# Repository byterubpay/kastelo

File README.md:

# Kastelo
This is the project to create an official ByteRub Hardware Wallet

1. [Safe, Vault](https://en.wikipedia.org/wiki/Esperanto), a place to store valuables
2. An open hardware ByteRub wallet

## Are you a tester looking for FW?
Please go to firmware/monezor and read the README there

## Disclaimers
- No hardware available
- Currently in the design and pre-fabrication stage

## Documentation
- Project documentation is being written
- [ByteRubpedia](https://getbyterub.org/knowledge-base/byterubpedia/) is recommended for a general introduction to the ByteRub-verse

## Developers
- Contributing advice is found in CONTRIBUTING.md (please review before submitting a pull request)

### Project Management
Follow the engineering pace of our project at:

[https://taiga.getbyterub.org/project/michael-rfc-hwallet-1-implementation/](https://taiga.getbyterub.org/project/michael-rfc-hwallet-1-implementation/)

## Support
- IRC: [Freenode](irc://chat.freenode.net/#byterub-hardware/)
- [ByteRub StackExchange](https://byterub.stackexchange.com/)
- [Mattermost](https://mattermost.getbyterub.org/byterub/channels/byterubhardware/)

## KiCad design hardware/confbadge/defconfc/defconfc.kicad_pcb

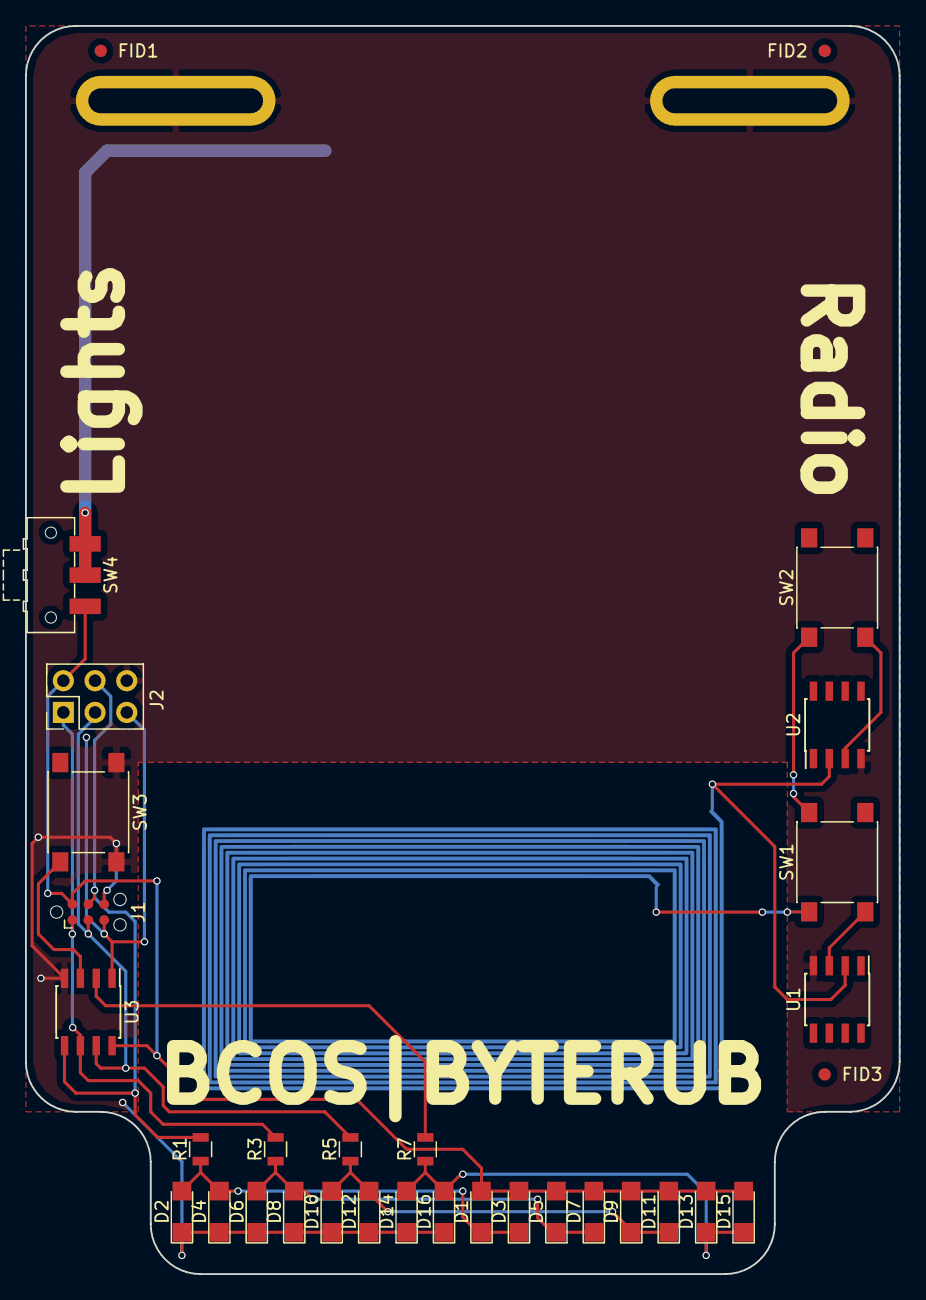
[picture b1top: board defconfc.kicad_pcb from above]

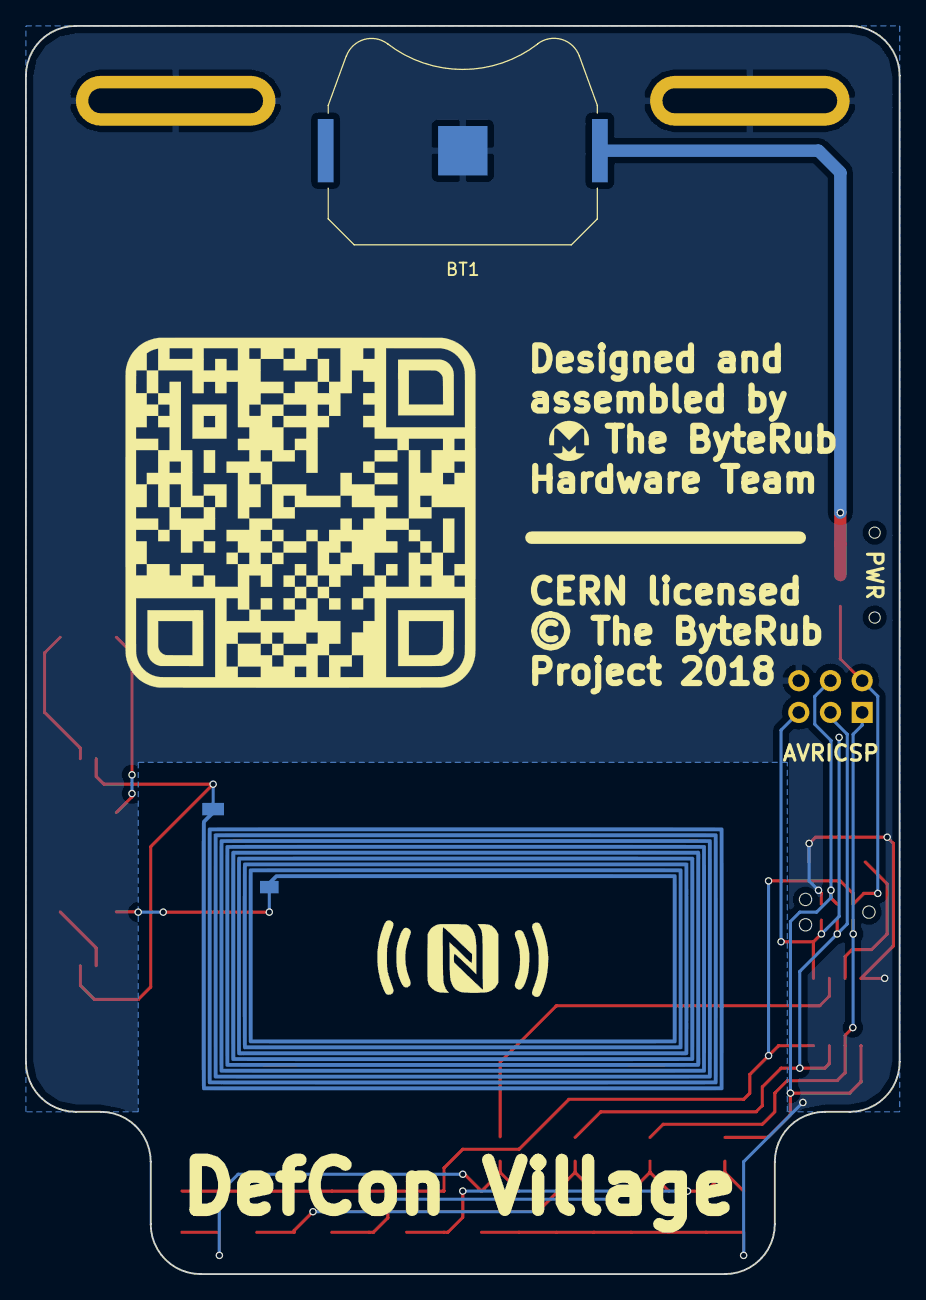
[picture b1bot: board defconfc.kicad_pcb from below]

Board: 2 copper layers, 70.0 x 100.0 mm, 39 parts (5 on the bottom side), 17 nets.

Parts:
AE1: Antenna_PCB; NFCAntennaloop
BT1: Battery_Cell; Keystone_3034_1x2032-Coincell
D1, D2, D3, D4, D5, D6, D7, D8, D9, D10, D11, D12, D13, D14, D15, D16: LED; LED_1206
FID1, FID2, FID3: Fiducial_Passermarke; Fiducial_1mm_Dia_2mm_Outer
G1: NFCRadiate; NFCGraphicsrear
G2: Kastelospecs; Kastelospecsqrcode
J1: Conn_02x03_Odd_Even; Tag-Connect_TC2030-IDC-NL
J2: Conn_02x03_Odd_Even; Pin_Header_Straight_2x03_Pitch2.54mm
L2: Graphbrand; ByteRublogokreis
LH1, LH2: Mounting-Lanyard; LanyardHole_16mm_Pad
R1, R3, R5, R7: 220; R_0805
SW1, SW2, SW3: SW_SPST; SW_SPST_PTS645
SW4: SW_SPDT; SW_SPDT_CK-JS102011SAQN
U1, U2: M24SR16-YMN6T/2; SOIC-8_3.9x4.9mm_Pitch1.27mm
U3: ATTINY13A-SSU; SOIC-8_3.9x4.9mm_Pitch1.27mm

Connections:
GND: BT1.2, D2.1, D4.1, D6.1, D8.1, D10.1, D12.1, D14.1, D16.1, J1.6, J2.6, LH1.1, LH2.1, SW3.2, U1.4, U2.4, U3.4
MISO: J1.1, J2.1, R3.2, U3.6
MOSI: J1.4, J2.4, R1.2, U3.5
unnamed: AE1.1, U1.2, U2.2
unnamed: AE1.2, SW1.1, SW2.1
unnamed: BT1.1, SW4.1, SW4.2
unnamed: D1.1, D2.2, D3.1, D4.2, R1.1
unnamed: D5.1, D6.2, D7.1, D8.2, R3.1
unnamed: D9.1, D10.2, D11.1, D12.2, R5.1
unnamed: D13.1, D14.2, D15.1, D16.2, R7.1
unnamed: SW1.2, U1.3
unnamed: SW2.2, U2.3
unnamed: SW3.1, U3.3
PB3: R7.2, U3.2
RST: J1.5, J2.5, U3.1
SCK: J1.3, J2.3, R5.2, U3.7
VCC: D1.2, D3.2, D5.2, D7.2, D9.2, D11.2, D13.2, D15.2, J1.2, J2.2, SW4.3, U3.8

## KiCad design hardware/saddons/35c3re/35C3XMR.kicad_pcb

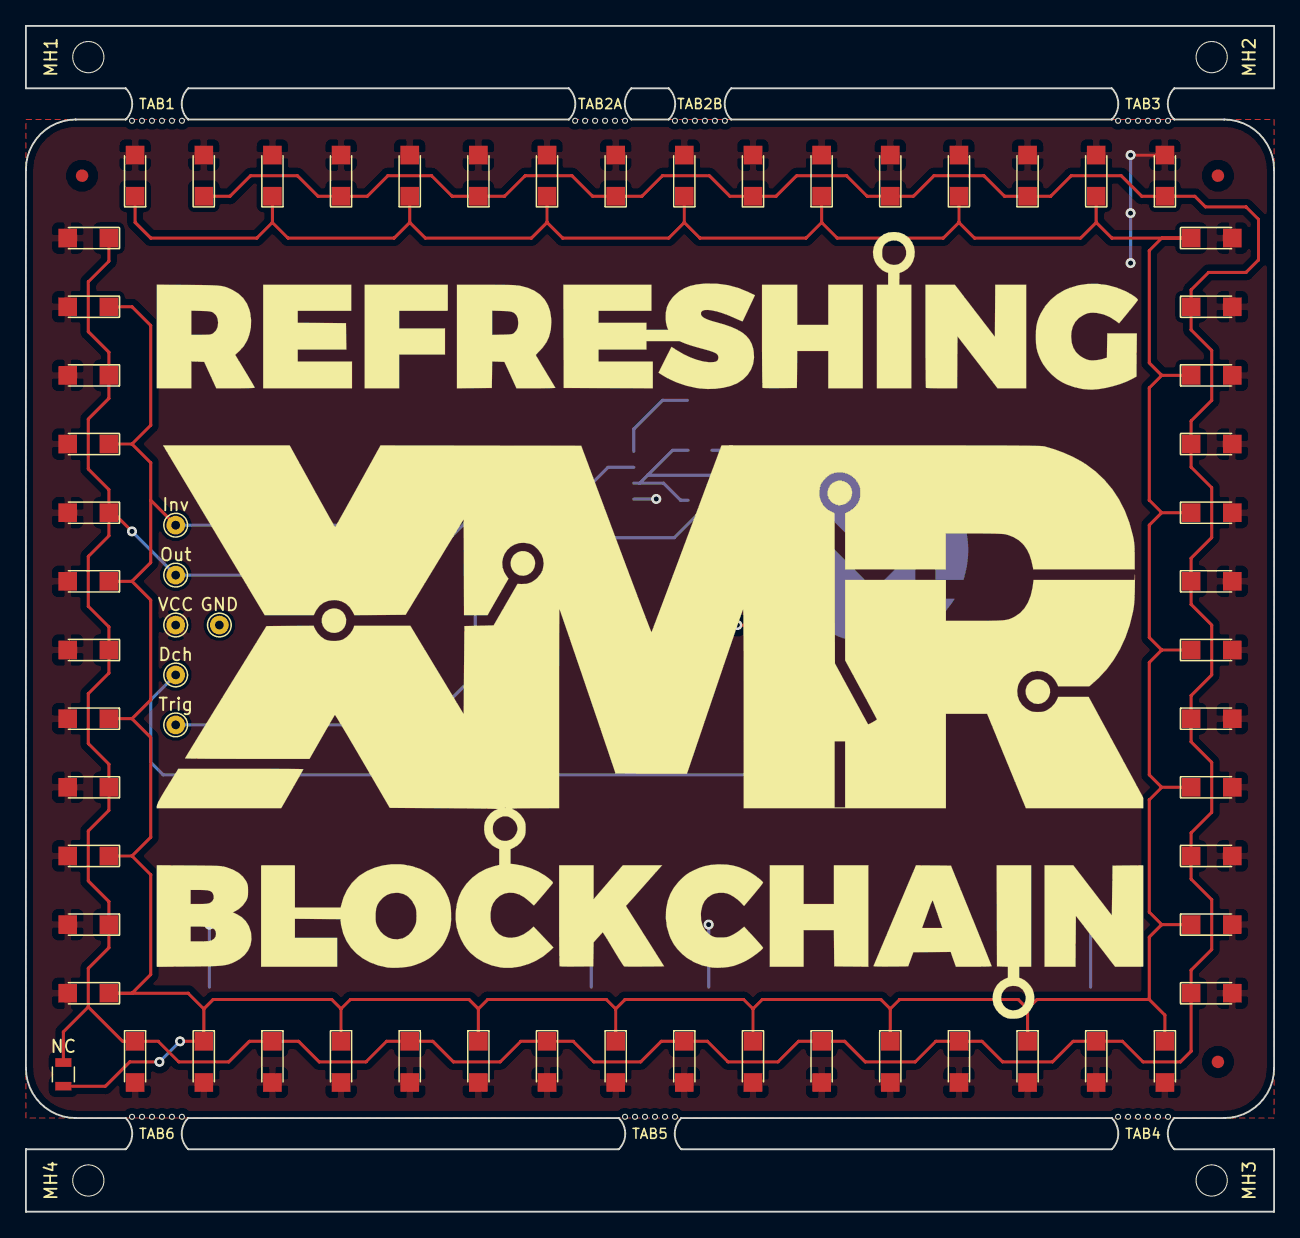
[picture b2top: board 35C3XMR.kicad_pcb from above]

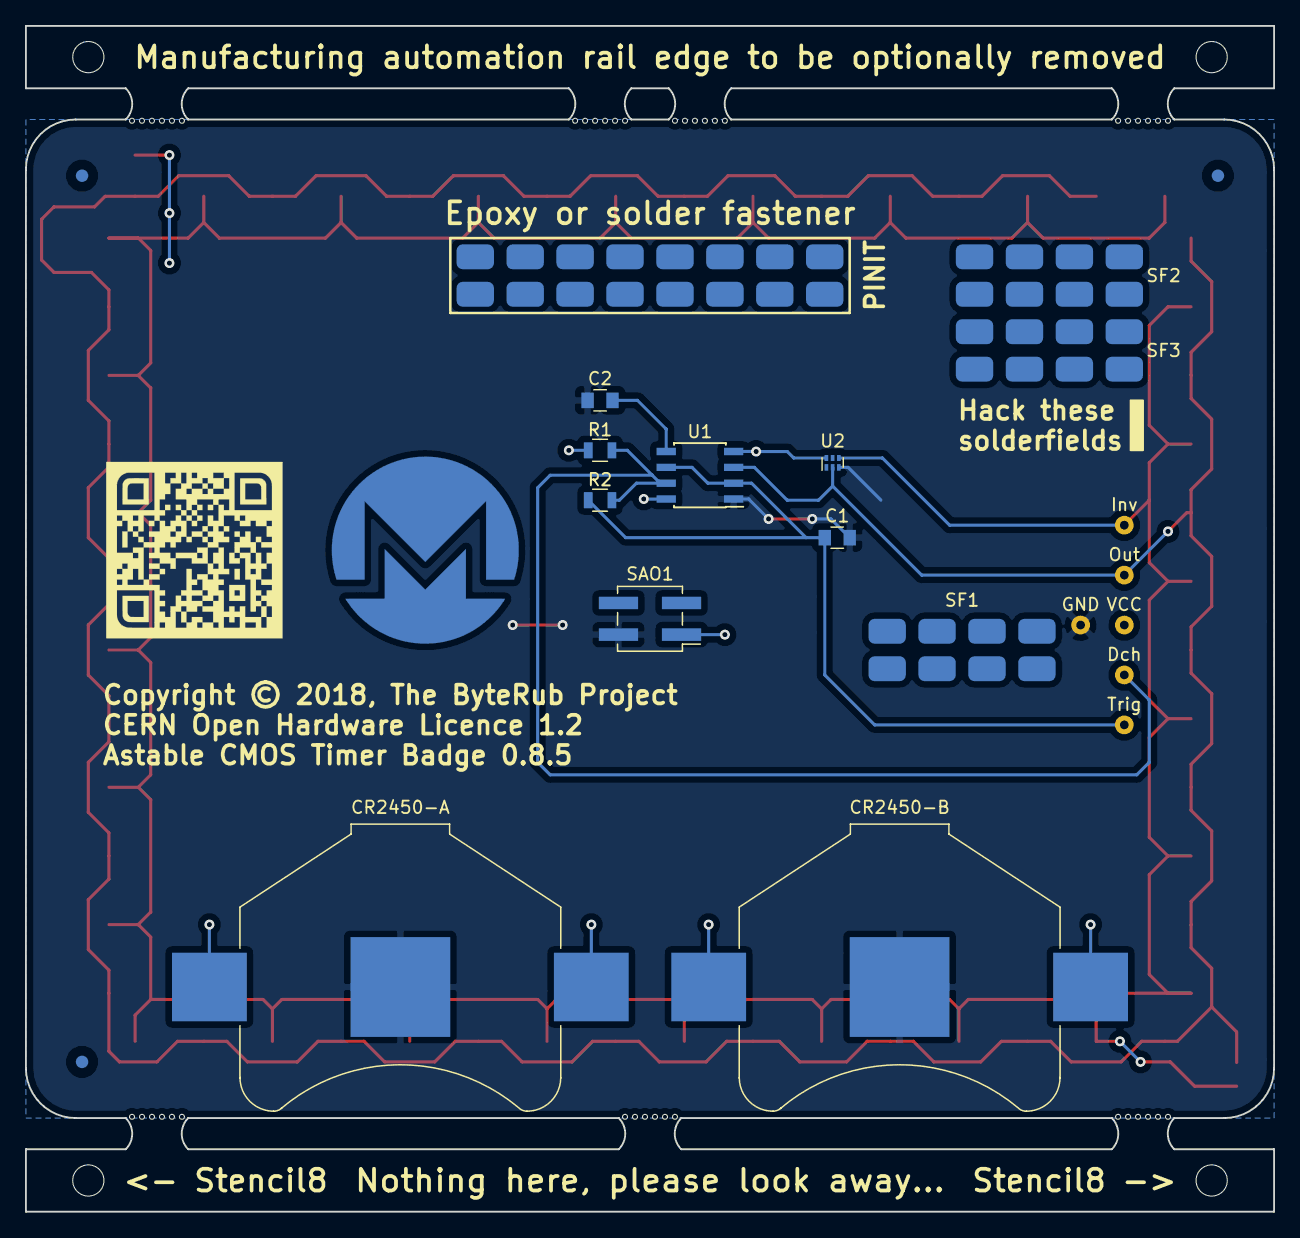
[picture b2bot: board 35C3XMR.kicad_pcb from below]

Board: 2 copper layers, 100.0 x 95.0 mm, 97 parts (19 on the bottom side), 7 nets.

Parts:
C1: 4,7uF; C_0805
C2: ,01uF; C_0805
CR2450-A, CR2450-B: Battery_Cell; BatteryHolder_Keystone_3008_1x2450
D1, D2, D3, D4, D5, D6, D7, D8, D9, D10, D11, D12, D13, D14, D15, D16, D17, D18, D19, D20, D21, D22, D23, D24, D25, D26, D27, D28, D29, D30, D31, D32, D33, D34, D35, D36, D37, D38, D39, D40, D41, D42, D43, D44, D45, D46, D47, D48, D49, D50, D51, D52, D53, D54, D55, D56: LED; LED_1206
Dch: TEST; TestPoint_THTPad_D1.5mm_Drill0.7mm
FID1, FID3, FID5: FiducialPassermarke-Top; Fiducial_1mm_Dia_2.54mm
FID2, FID4, FID6: FiducialPassermarke-Bot; Fiducial_1mm_Dia_2.54mm
G1: QRCOD; Kastelospecsqr
GND: TEST; TestPoint_THTPad_D1.5mm_Drill0.7mm
Inv: TEST; TestPoint_THTPad_D1.5mm_Drill0.7mm
LOGO1: 35C3Logo-funny; 35C3Funny
LOGO2: ByteRubball; ByteRubball_15mm
MH1, MH2, MH3, MH4: MountingHole_2.5mm
NC: Jumper; R_0805
Out: TEST; TestPoint_THTPad_D1.5mm_Drill0.7mm
R1: 10K; R_0805
R2: 100K; R_0805
SAO1: Shitty_conn; PinHeader_2x02_P2.54mm_Vertical_SMD
SF1, SF2, SF3, SF4, SF5: Soldfeld; Solderarea
TAB1, TAB2A, TAB2B, TAB3, TAB4, TAB5, TAB6: Panel_Mousetab_25mm_Single
Trig: TEST; TestPoint_THTPad_D1.5mm_Drill0.7mm
U1: TLC555; SOIC-8_3.9x4.9mm_P1.27mm
U2: NC7SZ04L6X; Fairchild_MicroPak-6_1.0x1.45mm_P0.5mm
VCC: TEST; TestPoint_THTPad_D1.5mm_Drill0.7mm

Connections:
+3V3: CR2450-A.1, CR2450-B.1, D1.2, D2.2, D3.2, D4.2, D5.2, D6.2, D7.2, D8.2, D9.2, D10.2, D11.2, D12.2, D13.2, D14.2, D15.2, D16.2, D17.2, D18.2, D19.2, D20.2, D21.2, D22.2, D23.2, D24.2, D25.2, D26.2, D27.2, D28.2, D29.2, D30.2, D31.2, D32.2, D33.2, D34.2, D35.2, D36.2, D37.2, D38.2, D39.2, D40.2, D41.2, D42.2, D43.2, D44.2, D45.2, D46.2, D47.2, D48.2, D49.2, D50.2, D51.2, D52.2, D53.2, D54.2, D55.2, D56.2, R1.2, SAO1.1, U1.4, U1.8, U2.6, VCC.1
GND: C1.2, C2.2, CR2450-A.2, CR2450-B.2, GND.1, SAO1.2, U1.1, U2.3
unnamed: C1.1, R2.2, Trig.1, U1.2, U1.6
unnamed: C2.1, U1.5
unnamed: D1.1, D3.1, D5.1, D7.1, D9.1, D11.1, D13.1, D15.1, D17.1, D19.1, D21.1, D23.1, D25.1, D27.1, D29.1, D31.1, D33.1, D35.1, D37.1, D39.1, D41.1, D43.1, D45.1, D47.1, D49.1, D51.1, D53.1, D55.1, Inv.1, NC.2, U2.4
unnamed: D2.1, D4.1, D6.1, D8.1, D10.1, D12.1, D14.1, D16.1, D18.1, D20.1, D22.1, D24.1, D26.1, D28.1, D30.1, D32.1, D34.1, D36.1, D38.1, D40.1, D42.1, D44.1, D46.1, D48.1, D50.1, D52.1, D54.1, D56.1, NC.1, Out.1, U1.3, U2.2
unnamed: Dch.1, R1.1, R2.1, U1.7

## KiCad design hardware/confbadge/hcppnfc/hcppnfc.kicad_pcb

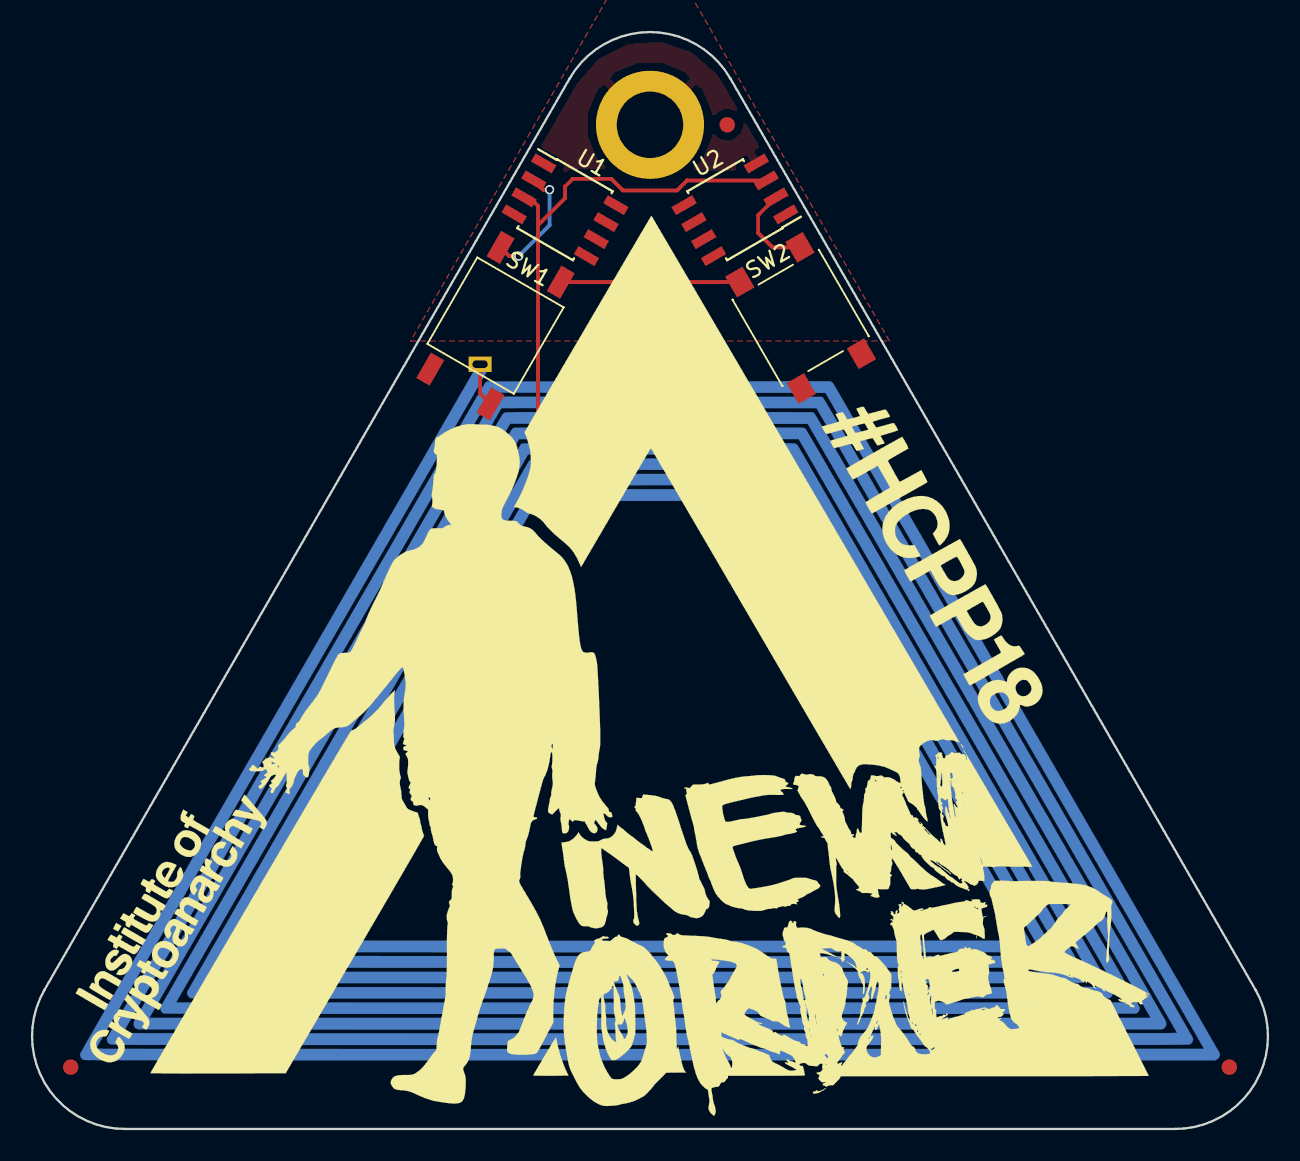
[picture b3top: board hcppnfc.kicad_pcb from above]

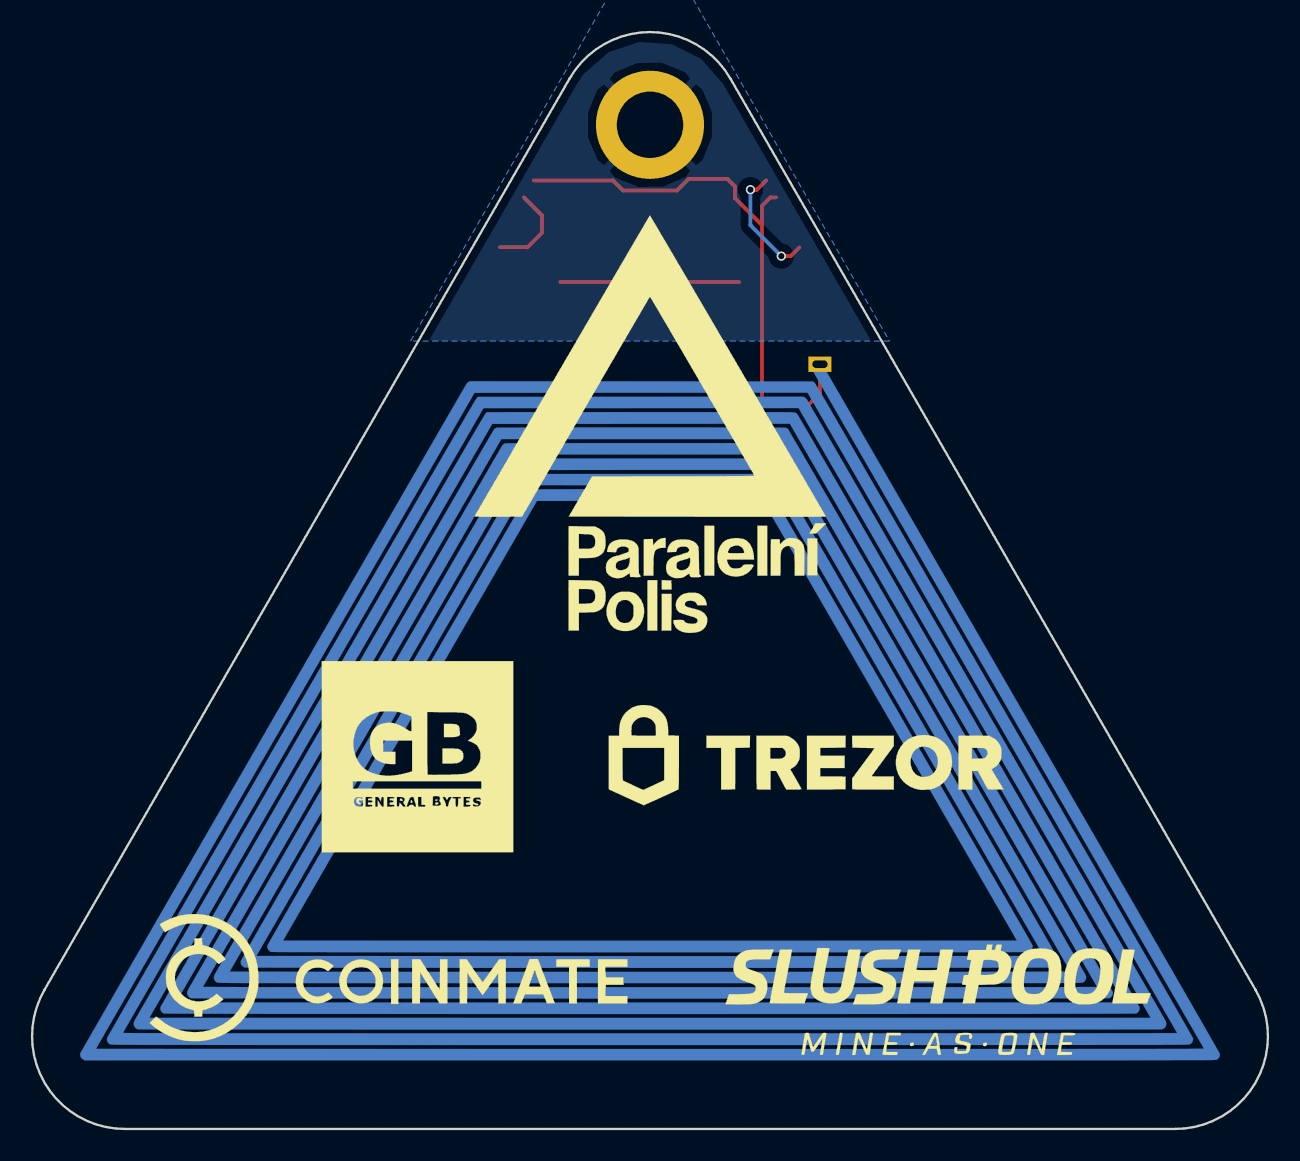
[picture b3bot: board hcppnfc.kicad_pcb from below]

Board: 2 copper layers, 80.0 x 71.0 mm, 13 parts (2 on the bottom side), 6 nets.

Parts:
AE1: Antenna_Loop; NFCAntennatall
FID1, FID2, FID3: Dummy_FIDUCIAL_Passermarke_Type1_RevE_Date16Nov20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; Fiducial_1mm_Dia_2mm_Outer
GFX*: ART_TRIANGLE; HCPPNewordtri
GFX*#2: ART_CONFYEAR; HCPPNewordconf
GFX*#3: ART_INSTCRYP; HCPPNewordinst
LOGO*: LOGO; HCPPSponsors
MH1: DUMMY_MOUNTING-HOLE_RevE_Date22jun2010; MountingHole_4.3mm_M4_ISO14580_Pad
SW1: SW_SPST; SW_SPST_K21102SP
SW2: SW_SPST; SW_SPST_PTS645
U1, U2: M24SR02-YMN; SOIC-8_3.9x4.9mm_Pitch1.27mm

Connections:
/ANTCON: AE1.2, U1.3, U2.3
GND: MH1.1, U1.4, U2.4
unnamed: AE1.1, SW1.1, SW2.1
unnamed: SW1.2, U1.2
unnamed: SW2.2, U2.2
VCC: U1.8, U2.8

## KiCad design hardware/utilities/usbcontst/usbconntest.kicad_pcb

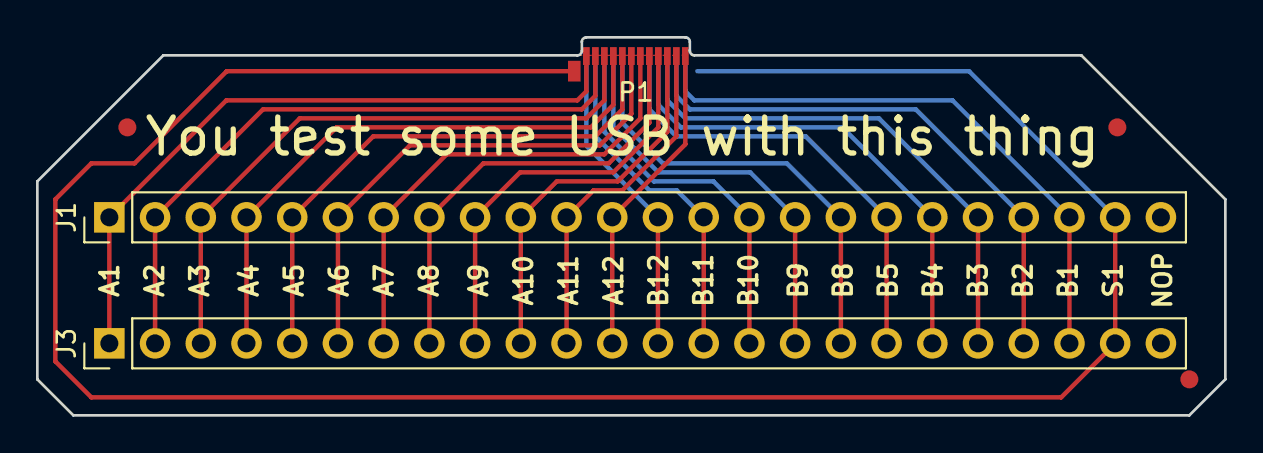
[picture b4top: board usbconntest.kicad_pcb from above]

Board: 2 copper layers, 66.0 x 21.0 mm, 6 parts (0 on the bottom side), 23 nets.

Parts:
FID1, FID2, FID3: Dummy_FIDUCIAL_Passermarke_Type1_RevE_Date16Nov20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; Fiducial_1mm_Dia_2mm_Outer
J1, J3: CONN_01X24; Pin_Header_Straight_1x24_Pitch2.54mm
P1: USB_C_Plug; USB_C_Plug_Molex_105444

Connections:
/A1: J1.1, J3.1, P1.A1
/A2: J1.2, J3.2, P1.A2
/A3: J1.3, J3.3, P1.A3
/A4: J1.4, J3.4, P1.A4
/A5: J1.5, J3.5, P1.A5
/A6: J1.6, J3.6, P1.A6
/A7: J1.7, J3.7, P1.A7
/A8: J1.8, J3.8, P1.A8
/A9: J1.9, J3.9, P1.A9
/A10: J1.10, J3.10, P1.A10
/A11: J1.11, J3.11, P1.A11
/A12: J1.12, J3.12, P1.A12
/B1: J1.22, J3.22, P1.B1
/B2: J1.21, J3.21, P1.B2
/B3: J1.20, J3.20, P1.B3
/B4: J1.19, J3.19, P1.B4
/B5: J1.18, J3.18, P1.B5
/B8: J1.17, J3.17, P1.B8
/B9: J1.16, J3.16, P1.B9
/B10: J1.15, J3.15, P1.B10
/B11: J1.14, J3.14, P1.B11
/B12: J1.13, J3.13, P1.B12
/S1: J1.23, J3.23, P1.S1

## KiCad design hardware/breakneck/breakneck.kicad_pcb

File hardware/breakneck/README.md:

# Hardware Breakneck Design

The Breakneck design includes rich features typical of a developer edition hardware wallet.

&nbsp;&nbsp;&nbsp;&nbsp;

## Getting Started

The Breakneck design consists of several files, some which are not tracked in revision control but are part of [project releases](https://github.com/byterubpay/kastelo/releases/).

* breakneck.pro (KiCad project)
* breakneck.sch (KiCad schematic)
* breakneck.kicad_pcb (KiCad layout)
* libraries (KiCad libraries)
* modules (KiCad footprints)

Fabrication subdirectories contain files meant for printing, assembly, and other production work.

* billofmat (Bill of materials generated from the layout)
* fabpanel (Gerber files for printing panelized PCBs)
* fabraster (3D rendition of a single PCB layout)
* fabsingle (Gerber files for printing single PCBs)
* fabvector (Vector files useful for mechanical engineering)

Other subdirectories exist to provide conveniently formatted files generated from source.

* release (Tested distribution release files containing change logs)
* schematic (Copy of breakneck.sch converted to common graphic formats)

A Makefile serves project management tasks allowing for scripting and automation.

* Makefile (A GNU Makefile facilitating command line project tasks)

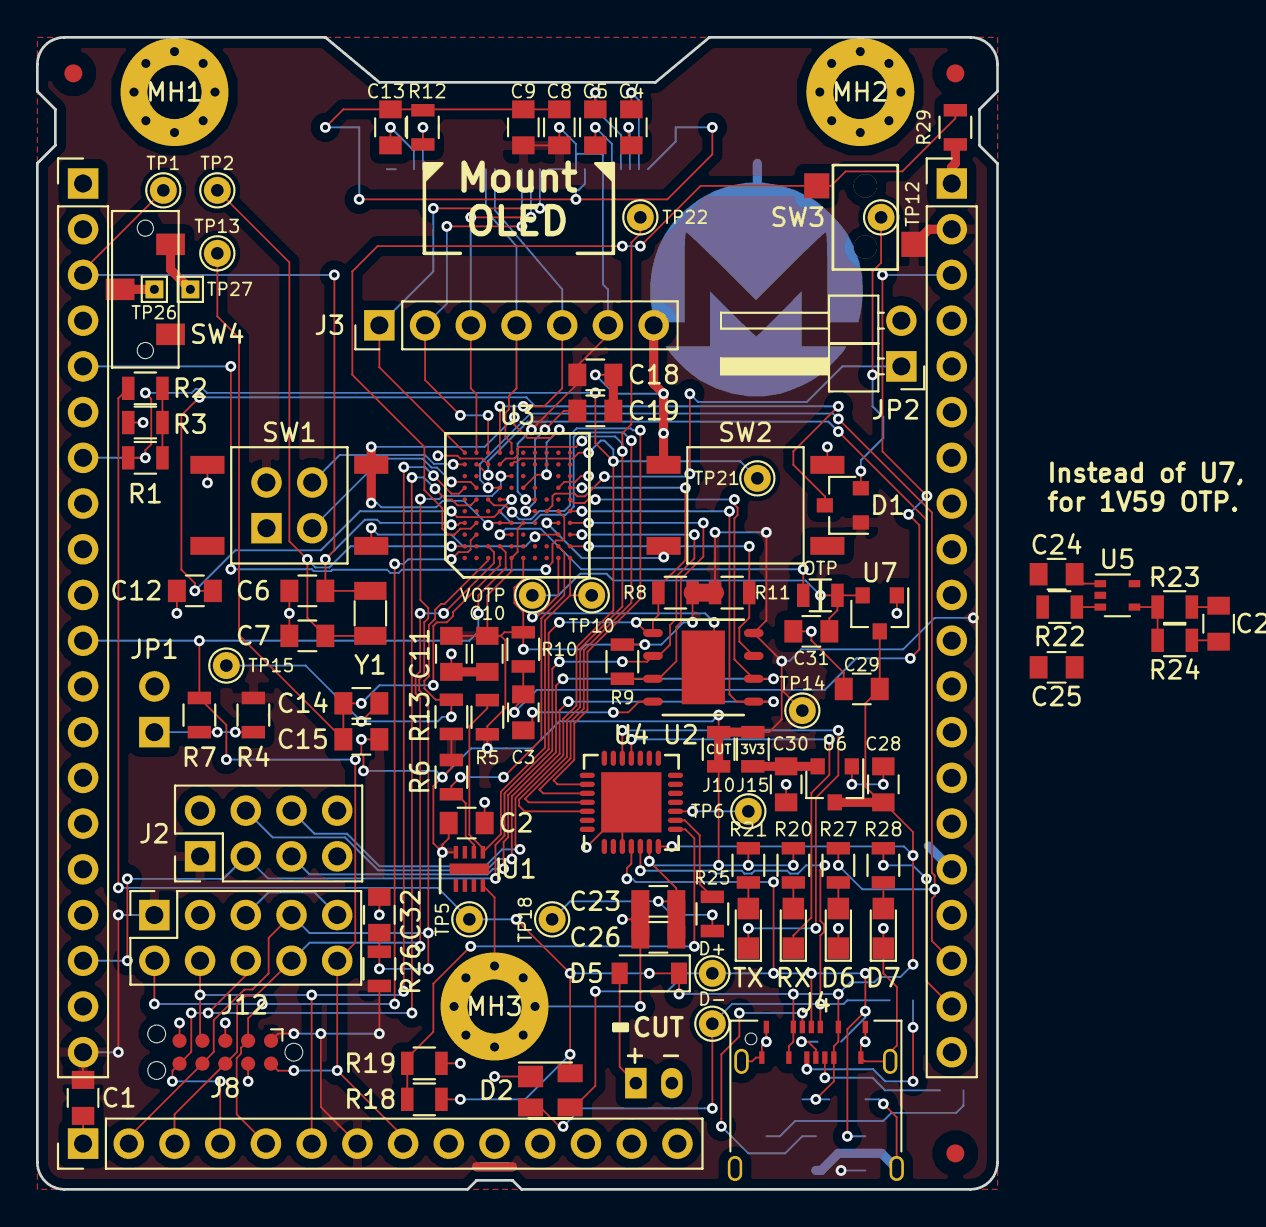
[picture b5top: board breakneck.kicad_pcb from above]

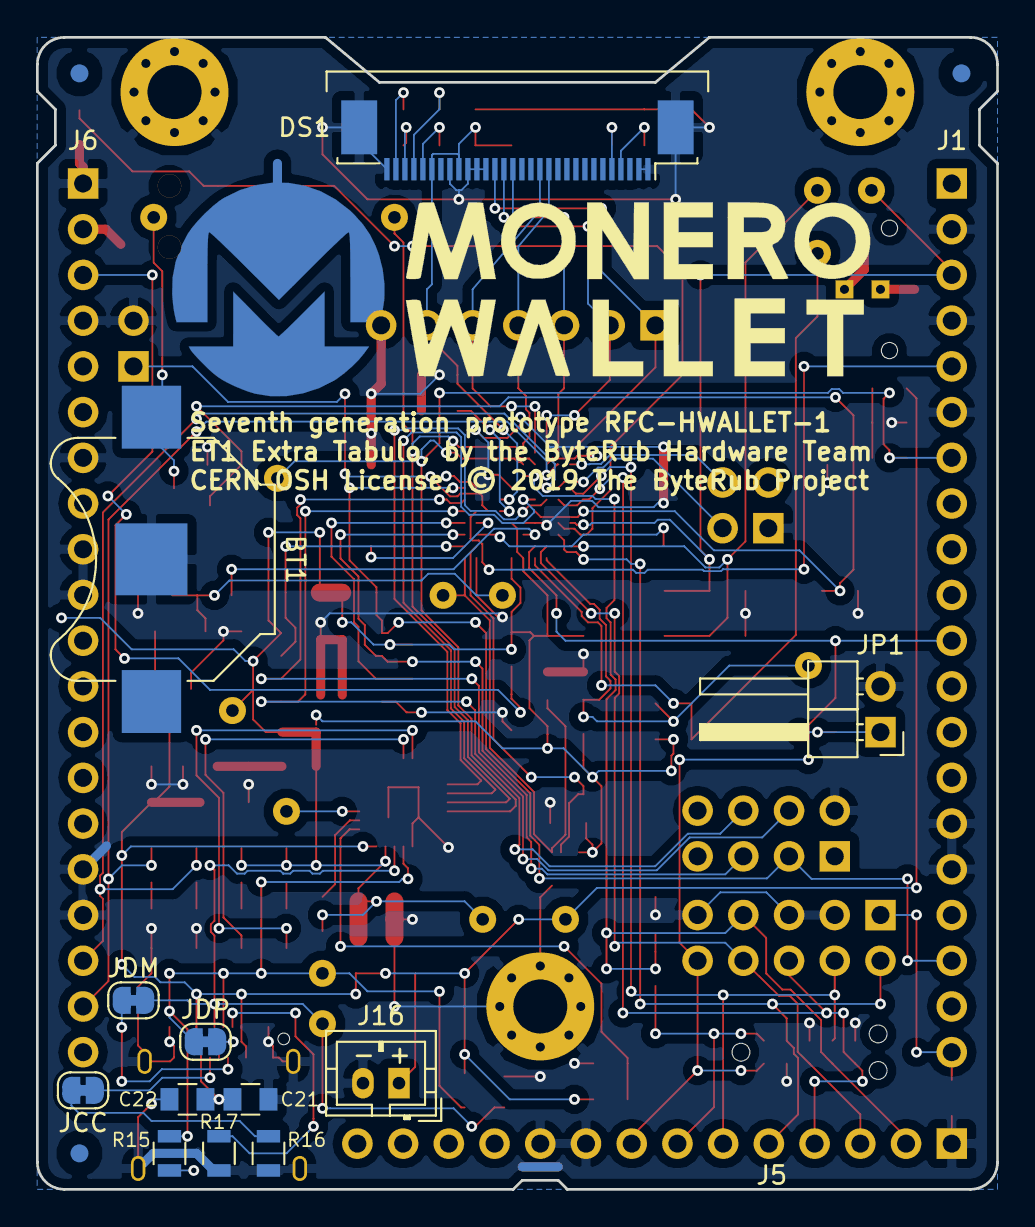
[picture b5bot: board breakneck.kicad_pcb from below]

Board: 2 copper layers, 53.3 x 64.0 mm, 124 parts (17 on the bottom side), 79 nets.

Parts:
BT1: Battery_Cell; Keystone_3000_1x12mm-CoinCell
C1, C2, C8, C11, C15, C19, C21, C22, C23, C25, C26: 100nF; C_0805
C3, C14: 470nF; C_0805
C4, C5, C9, C10, C12, C18, C28, C29, C30, C31, C32: 1uF; C_0805
C6, C7: 15pF; C_0805
C13, C24, C27: 2.2uF; C_0805
D1: BAT54C; SOT-23
D2: SP0503BAHTG; SOT-143
D5: D_PMEG; D_SOD-123
D6, D7: LED; LED_0805
D+: TUSBP; TestPoint_THTPad_D1.5mm_Drill0.7mm
D-: TUSBN; TestPoint_THTPad_D1.5mm_Drill0.7mm
DS1: ER-CON30; Eastrising_ER-CON30HT-1_01x30_P0.50mm
FID1, FID2, FID3, FID4, FID5, FID6: Fiducial-PCB; Fiducial_1mm_Dia_2.54mm_Outer_CopperTop
J1: CONN_WEST; Pin_Header_Straight_1x20_Pitch2.54mm
J2: CONN_DEDI; Pin_Header_Straight_2x04_Pitch2.54mm
J3: CONN_OLED; Socket_Strip_Straight_1x07_Pitch2.54mm
J4: USB_C_Rcpt_Min; USBC_Rcpt_Min_12401610E4-2A
J5: CONN_SOUTH; Pin_Header_Straight_1x14_Pitch2.54mm
J6: CONN_EAST; Pin_Header_Straight_1x20_Pitch2.54mm
J8: CONN_JTAG_TC; Tag-Connect_TC2050-IDC-NL
J10, J15: GS2; R_0805
J12: CONN_JTAG_6P; PinSocket_2x05_P2.54mm_Vertical
J16: CONN_JST; JST_PH_B2B-PH-K_02x2.00mm_Straight
JCC: SJC2; Solderjump-2NCRndpad
JDM: SJC2; Solderjump-2NCRndpad
JDP: SJC2; Solderjump-2NCRndpad
JP1, JP2: Jumper; Pin_Header_Angled_1x02_Pitch2.54mm
LOGO1: ByteRublogo-mid; ByteRubCircleCombi
LOGOTXT1: ByteRublogo-txt; ByteRubTextSilk
MH1, MH2, MH3: Mountinghole-440; MountingHole_3mm_Pad_Via
OTP: 150; R_0805
R1, R7: 0; R_0805
R2: 12K; R_0805
R3: 22K; R_0805
R4, R29: 10K; R_0805
R5, R6: 3.9K; R_0805
R8, R9, R11, R26: 100K; R_0805
R10: 10; R_0805
R12: 390K; R_0805
R13: 100; R_0805
R15: 1.5K; R_0805
R16, R17: 2.4K; R_0805
R18: 22.1K; R_0805
R19: 47.5K; R_0805
R20, R21: 220; R_0805
R22, R25: 1K; R_0805
R23: 130K; R_0805
R24: 220K; R_0805
R27, R28: 150; R_0805
RX: LED; LED_0805
SW1, SW2: SW_SPST; SW_SPST_K21102SP
SW3: SW_SPST; SW_SPST_ESE11MV1
SW4: SW_SPDT; SW_SPDT_CLSB-12A
TP1: TCRY1; TestPoint_THTPad_D1.5mm_Drill0.7mm
TP2: TCRY2; TestPoint_THTPad_D1.5mm_Drill0.7mm
TP5: T5V; TestPoint_THTPad_D1.5mm_Drill0.7mm
TP6: TWHAT; TestPoint_THTPad_D1.5mm_Drill0.7mm
TP10: TSED; TestPoint_THTPad_D1.5mm_Drill0.7mm
TP12: TBT; TestPoint_THTPad_D1.5mm_Drill0.7mm
TP13: TPLL2; TestPoint_THTPad_D1.5mm_Drill0.7mm
TP14: T3V3; TestPoint_THTPad_D1.5mm_Drill0.7mm
TP15: TPLL1; TestPoint_THTPad_D1.5mm_Drill0.7mm
TP18: TVDD; TestPoint_THTPad_D1.5mm_Drill0.7mm
TP21: TUART_TX; TestPoint_THTPad_D1.5mm_Drill0.7mm
TP22: TUART_RX; TestPoint_THTPad_D1.5mm_Drill0.7mm
TP26, TP27: TEST; TestPoint_THTPad_1.0x1.0mm_Drill0.5mm
TX: LED; LED_0805
U1: ATECC508A; DFN-8-1EP_2x3mm_Pitch0.5mm
U2: SST26VF064B; DFN-S-8-1EP_6x5mm_Pitch1.27mm
U3: CEC1702; WFBGACEC1702
U4: CP2102N; QFN-28-1EP_5x5mm_Pitch0.5mm
U5: MIC5377YC5; SOT-353_SC-70-5
U6: LN6206P33M; SOT-23
U7: LN6206P15M; SOT-23
VOTP: VOTP; TestPoint_THTPad_D1.5mm_Drill0.7mm
X1: Badgelife_shitty; Badgelife-Shitty-2x2
Y1: Crystal; Crystal_SMD_3215-2Pin_3.2x1.5mm

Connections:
+1V5: C27.1, C31.1, OTP.2, R23.1, U5.5, U7.2, VOTP.1
+3V3: C1.2, C2.1, C8.1, C9.1, C10.1, C11.1, C15.1, C18.2, C19.2, D1.1, DS1.6, DS1.9, J1.20, J2.1, J3.6, J5.7, J6.2, J8.1, J10.1, J12.1, J15.1, R4.1, R5.2, R6.2, R8.2, R9.2, R10.1, R11.2, R13.1, R15.2, R26.1, SW3.2, TP14.1, U1.8, U2.8, U3.E1, U3.F1, U3.F4, U3.G5, U3.G6, X1.1
+5V: C21.1, C22.1, C24.1, C28.1, C29.1, D2.4, D5.1, J4.A4, J4.A9, J4.B4, J4.B9, R2.2, R18.1, R22.1, TP5.1, U4.7, U5.1, U6.3, U7.3
/BOOT: JP2.1, U3.H5
/BRIDGE_CTS: U3.C6, U4.23
/BRIDGE_RTS: U3.D6, U4.24
/BRIDGE_RX: J1.8, TP22.1, U3.D9, U4.25
/BRIDGE_TX: J1.7, R1.2, TP21.1, U3.E9, U4.26
/CLK_FB: J1.5, U3.J5
/CLK_IN: C6.2, J1.3, TP1.1, U3.A4, Y1.1
/CLK_OUT: C7.1, TP2.1, U3.A2, Y1.2
/CWLED3: J6.20, U3.C9
/FLASH_CS: J1.18, J2.3, R8.1, U2.1, U3.K7
/FLASH_SCK: J2.4, U2.6, U3.K6
/FLASH_SIO0: J2.6, U2.5, U3.K5
/FLASH_SIO1: J2.5, U2.2, U3.K3
/FLASH_SIO2: R9.1, U2.3, U3.K4
/FLASH_SIO3: R11.1, U2.7, U3.K2
/JTAG_TCK: J5.6, J8.4, J12.4, U3.A7
/JTAG_TDI: J5.3, J8.8, J12.8, U3.C2
/JTAG_TDO: J5.4, J8.6, J12.6, U3.B6
/JTAG_TMS: J5.5, J8.2, J12.2, U3.B3
/JTAG_TRST: C32.1, J5.2, J8.7, J12.7, R26.2, U3.E8
/OLED_D0: DS1.18, J3.5, U3.D10
/OLED_D1: DS1.19, J3.4, U3.E10
/OLED_DC: DS1.15, J3.2, U3.C10
/OLED_~CS~: DS1.13, J3.1, U3.A10
/OLED_~RES~: DS1.14, J3.3, U3.B10
/PWMLED0: J6.18, R27.2, U3.D7
/PWMLED1: J6.19, R28.2, U3.B9
/RESET: J1.11, J5.8, J8.10, J12.10, R7.1, U3.D2
/SAO_SCL: U3.B7, X1.3
/SAO_SDA: U3.A9, X1.4
/SDCARD_MISO: J1.13, U3.F10
/SDCARD_MOSI: J1.14, U3.B2
/SDCARD_SCK: J1.12, U3.G4
/SHUNTH: C3.1, J6.3, R10.2
/TRIGGER: J1.10, U3.J7
/USB_N: D2.2, D-.1, J4.A7, JDM.2, U4.5
/USB_P: D2.3, D+.1, J4.A6, JDP.2, R15.1, U4.4
/VIN_OTP: C25.1, OTP.1, U3.E3
GND: BT1.2, C1.1, C2.2, C3.2, C6.1, C7.2, C8.2, C9.2, C10.2, C11.2, C12.2, C13.2, C18.1, C19.1, C21.2, C22.2, C23.2, C24.2, C25.2, C26.2, C27.2, C28.2, C29.2, C30.2, C31.2, C32.2, D2.1, D6.1, D7.1, DS1.1, DS1.8, DS1.10, DS1.11, DS1.12, DS1.29, DS1.30, J1.2, J1.4, J1.6, J1.15, J1.16, J2.2, J3.7, J4.A1, J4.A12, J4.B1, J4.B12, J4.S1, J5.1, J5.9, J5.10, J6.1, J6.4, J6.7, J6.9, J6.10, J6.16, J6.17, J8.3, J8.5, J8.9, J12.3, J12.5, J12.9, J16.2, JP1.2, JP2.2, MH1.1, MH2.1, MH3.1, R3.1, R12.1, R16.1, R17.1, R19.2, R24.2, R29.1, SW1.1, SW2.1, U1.4, U2.4, U2.9, U3.D4, U3.E4, U3.F7, U3.J1, U4.3, U4.29, U5.2, U6.1, U7.1, X1.2
unnamed: BT1.1, D1.2, TP12.1
unnamed: C4.1, DS1.2
unnamed: C4.2, DS1.3
unnamed: C5.1, DS1.4
unnamed: C5.2, DS1.5
unnamed: C12.1, D1.3, U3.D5
unnamed: C13.1, DS1.27
unnamed: C14.1, R13.2, TP15.1, U3.C1
unnamed: C14.2, C15.2, TP13.1, U3.D1
unnamed: C23.1, C26.1, J10.2, R20.1, R21.1, R25.1, TP18.1, U4.6
unnamed: C30.1, J15.2, U6.2
unnamed: RX.1, U4.18
unnamed: R20.2, RX.2
unnamed: TX.1, U4.19
unnamed: R21.2, TX.2
unnamed: D5.2, SW4.2, TP26.1
unnamed: D6.2, R27.1
unnamed: D7.2, R28.1
unnamed: DS1.26, R12.2
unnamed: J4.A5, R17.2
unnamed: J4.B5, JCC.1
unnamed: J4.B6, JDP.1
unnamed: J4.B7, JDM.1
unnamed: J16.1, SW4.3, TP27.1
unnamed: JP1.1, R4.2, R7.2
unnamed: JCC.2, R16.2
unnamed: R1.1, R2.1, R3.2
unnamed: R5.1, TP10.1, U1.5, U3.K1
unnamed: R6.1, U1.6, U3.J2
unnamed: R18.2, R19.1, U4.8
unnamed: R22.2, U5.3
unnamed: R23.2, R24.1, U5.4
unnamed: R25.2, U4.9
unnamed: R29.2, SW3.1, U3.B4
unnamed: SW1.2, U3.J3
unnamed: SW2.2, U3.J4
unnamed: TP6.1, U4.10

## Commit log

2020-02-14 master
2020-02-20 master ByteRub
2020-02-20 master byterub-coin

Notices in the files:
hardware/breakneck/breakneck.kicad_pcb:
Copyright © 2019, The ByteRub Project
CERN OSH License, © 2019 The ByteRub Project
hardware/confbadge/defconfc/defconfc.kicad_pcb:
Copyright © 2018, The ByteRub Project
© The ByteRub
hardware/saddons/35c3re/35C3XMR.kicad_pcb:
CERN Open Hardware Licence 1.2
